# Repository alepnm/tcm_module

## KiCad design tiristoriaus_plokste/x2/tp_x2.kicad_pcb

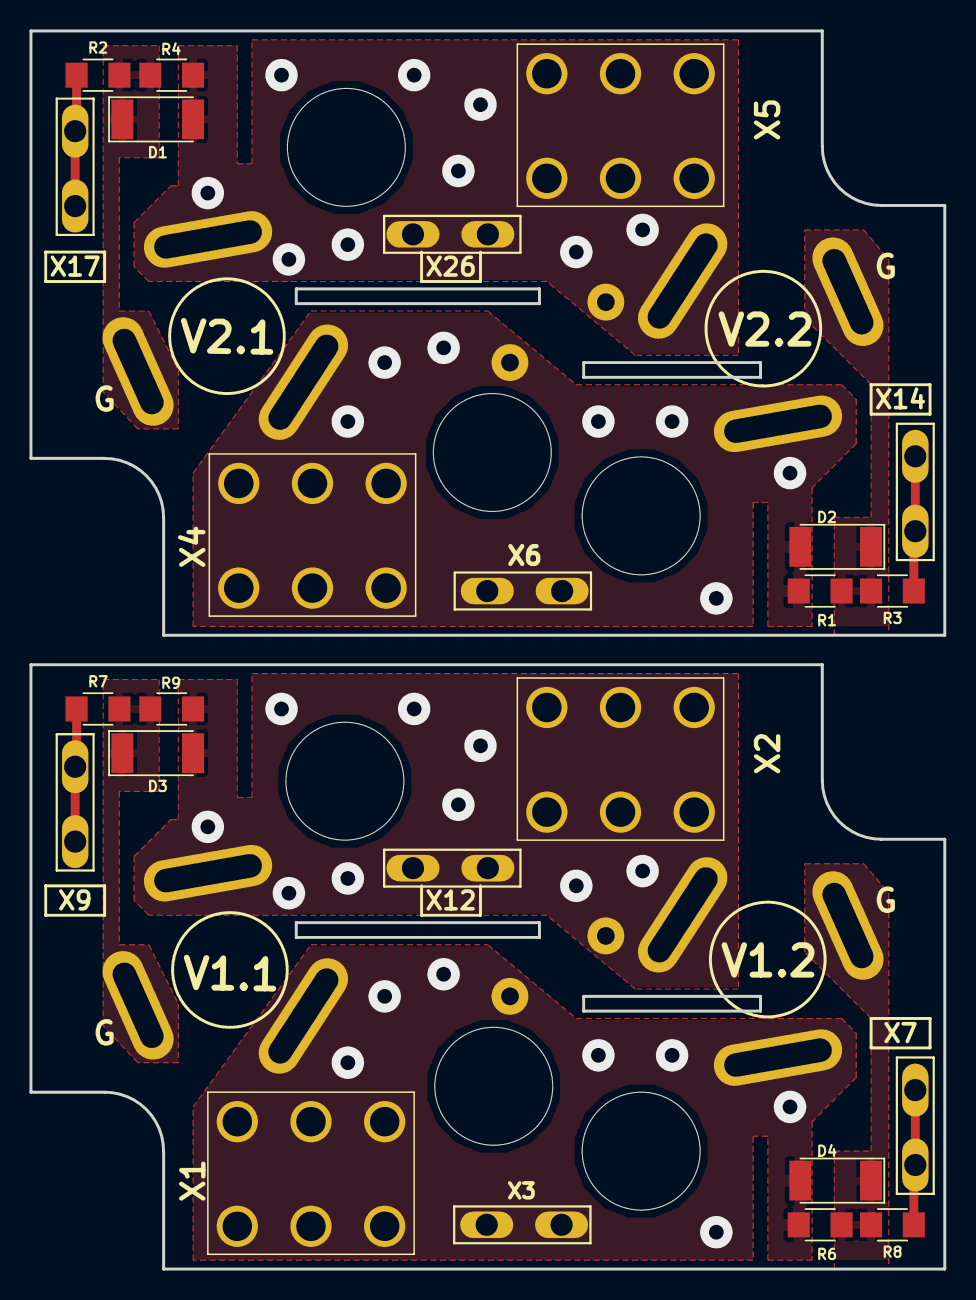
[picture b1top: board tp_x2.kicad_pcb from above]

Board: 2 copper layers, 62.0 x 84.0 mm, 32 parts (0 on the bottom side), 12 nets.

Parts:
D1, D2, D3, D4: LL4007; D_MELF
H1, H2, H3, H4: Conn_01x01; SolderWirePad_single_1mmDrill
R1, R4, R6, R9: 1k; R_1206
R2, R3, R7, R8: 470R; R_1206
V1.1, V1.2, V2.1, V2.2: BTW67; RD91
X1: LD1; Solder_Terminal_M3
X2: PH1; Solder_Terminal_M3
X3, X6, X7, X9, X12, X14, X17, X26: Faston_6.3x08x14; Faston_6.3x0.8x14
X4: LD3; Solder_Terminal_M3
X5: PH3; Solder_Terminal_M3

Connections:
/CTRL1A: R7.1, X9.1
/CTRL1B: R8.1, X7.1
/CTRL3A: R2.1, X17.1
/CTRL3B: R3.1, X14.1
/LD1: D4.2, H1.1, R6.1, V1.1.1, V1.2.3, X1.1, X3.1
/LD3: D2.2, H3.1, R1.1, V2.1.1, V2.2.3, X4.1, X6.1
/PH1: D3.2, H2.1, R9.1, V1.1.3, V1.2.1, X2.1, X12.1
/PH3: D1.2, H4.1, R4.1, V2.1.3, V2.2.1, X5.1, X26.1
unnamed: D1.1, R2.2, R4.2, V2.1.2
unnamed: D2.1, R1.2, R3.2, V2.2.2
unnamed: D3.1, R7.2, R9.2, V1.1.2
unnamed: D4.1, R6.2, R8.2, V1.2.2

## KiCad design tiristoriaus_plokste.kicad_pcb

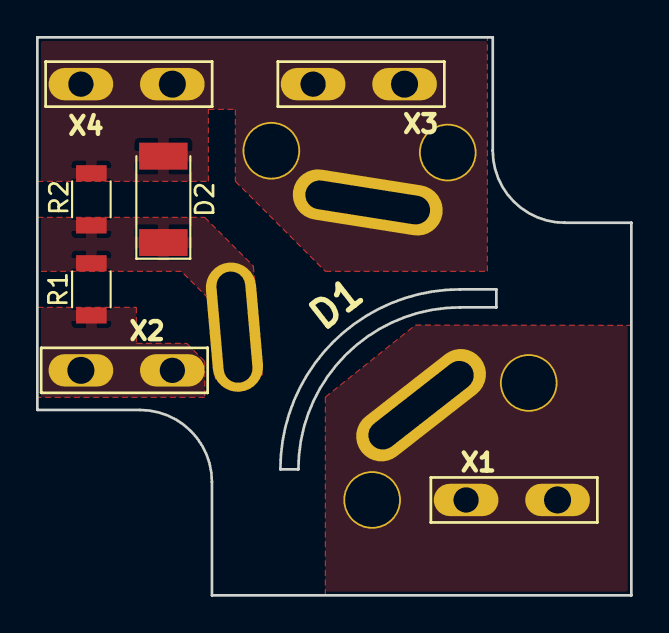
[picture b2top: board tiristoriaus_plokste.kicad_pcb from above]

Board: 2 copper layers, 33.0 x 31.0 mm, 8 parts (0 on the bottom side), 4 nets, no tracks yet.

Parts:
D1: BTW67; RD91
D2: LL4007; D_MELF
R1: 470R; R_1206
R2: 1k; R_1206
X1: A; Faston_6.3x0.8x14
X2, X4: Faston_6.3x08x14; Faston_6.3x0.8x14
X3: K; Faston_6.3x0.8x14

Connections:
/A: D1.1, X1.1
/C: D1.3, D2.2, R2.1, X3.1, X4.1
/CTRL: R1.1, X2.1
unnamed: D1.2, D2.1, R1.2, R2.2

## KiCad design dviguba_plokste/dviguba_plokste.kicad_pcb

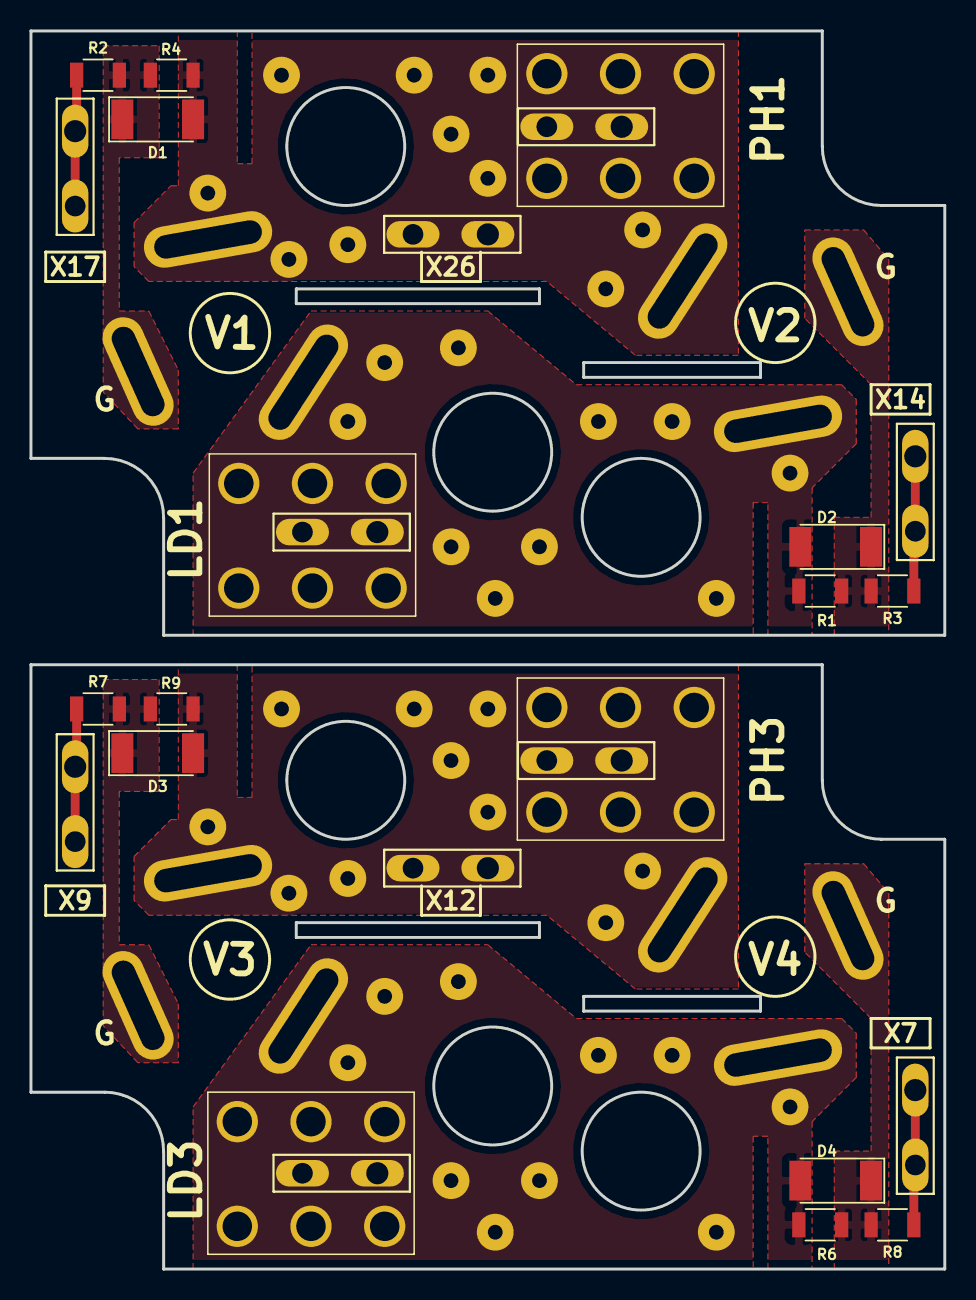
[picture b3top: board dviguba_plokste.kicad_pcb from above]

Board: 2 copper layers, 62.0 x 84.0 mm, 70 parts (0 on the bottom side), 12 nets.

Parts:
D1, D2, D3, D4: LL4007; D_MELF
H1, H2, H3, H4, H5, H6, H7, H8, H9, H10, H11, H12, H13, H14, H15, H16, H17, H18, H19, H20, H21, H22, H23, H24, H25, H26, H27, H28, H29, H30, H32, H33, H34, H35, H36, H37, H38, H39, H40: Conn_01x01; SolderWirePad_single_1mmDrill
H31: eConn_01x01; SolderWirePad_single_1mmDrill
R1, R4, R6, R9: 1k; R_1206
R2, R3, R7, R8: 470R; R_1206
V1, V2, V3, V4: BTW67; RD91
X1: LD3; Solder_Terminal_M6
X2: PH3; Solder_Terminal_M6
X3, X6, X7, X8, X9, X10, X12, X14, X17, X26: Faston_6.3x08x14; Faston_6.3x0.8x14
X4: LD1; Solder_Terminal_M6
X5: PH1; Solder_Terminal_M6

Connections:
/CTRL1A: R2.1, X17.1
/CTRL1B: R3.1, X14.1
/CTRL3A: R7.1, X9.1
/CTRL3B: R8.1, X7.1
/LD1: D2.2, H1.1, H2.1, H3.1, H4.1, H5.1, H6.1, H7.1, H8.1, H9.1, H10.1, R1.1, V1.1, V2.3, X3.1, X4.1
/LD3: D4.2, H21.1, H22.1, H23.1, H24.1, H25.1, H26.1, H27.1, H28.1, H29.1, H30.1, R6.1, V3.1, V4.3, X1.1, X8.1
/PH1: D1.2, H11.1, H12.1, H13.1, H14.1, H15.1, H16.1, H17.1, H18.1, H19.1, H20.1, R4.1, V1.3, V2.1, X5.1, X6.1, X26.1
/PH3: D3.2, H31.1, H32.1, H33.1, H34.1, H35.1, H36.1, H37.1, H38.1, H39.1, H40.1, R9.1, V3.3, V4.1, X2.1, X10.1, X12.1
unnamed: D1.1, R2.2, R4.2, V1.2
unnamed: D2.1, R1.2, R3.2, V2.2
unnamed: D3.1, R7.2, R9.2, V3.2
unnamed: D4.1, R6.2, R8.2, V4.2

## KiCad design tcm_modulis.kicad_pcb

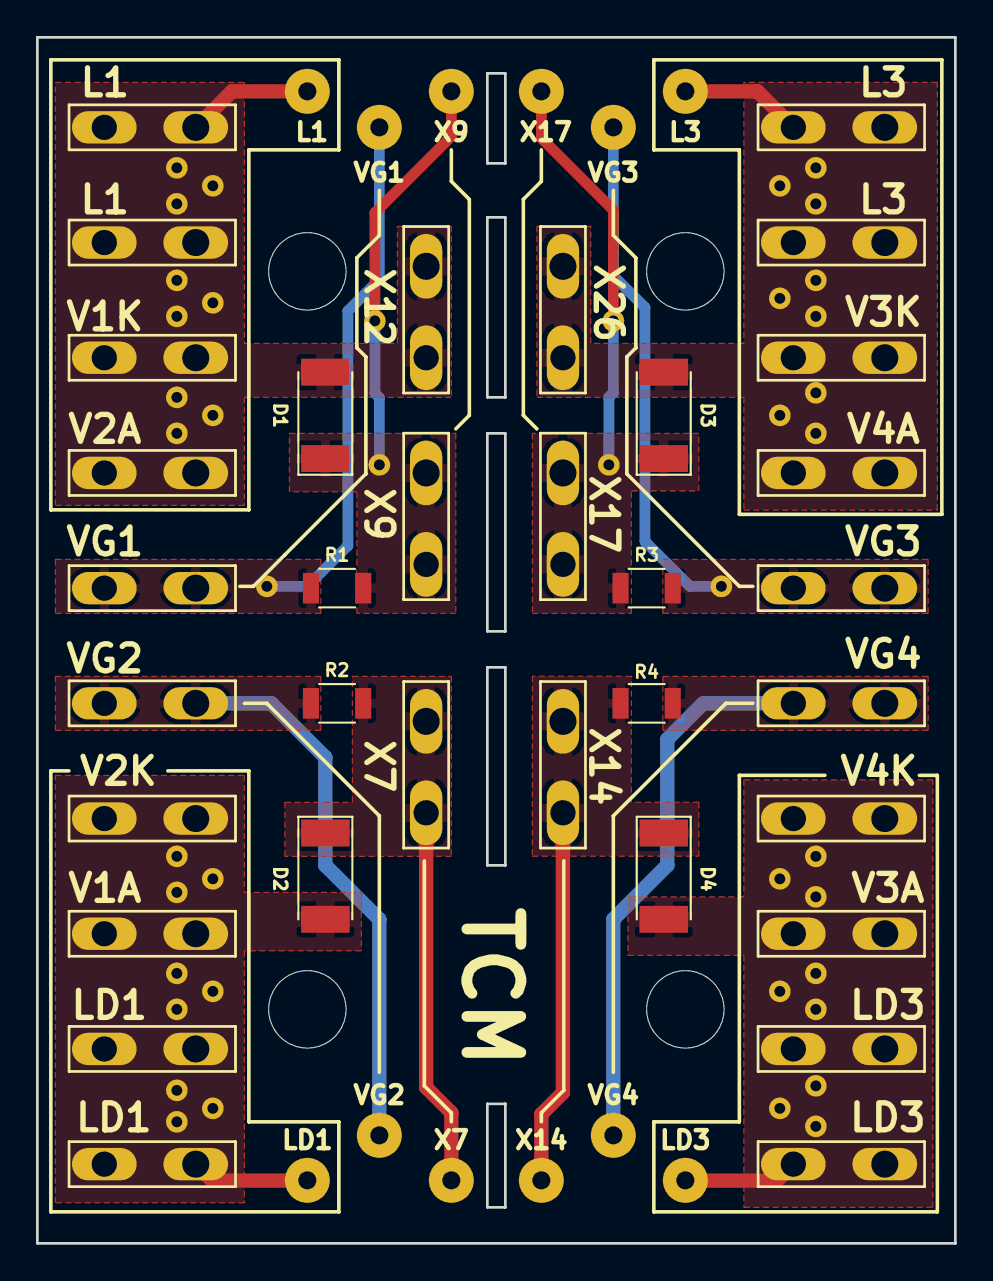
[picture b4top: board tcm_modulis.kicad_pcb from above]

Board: 2 copper layers, 51.0 x 67.0 mm, 34 parts (0 on the bottom side), 12 nets.

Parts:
D1, D2, D3, D4: LL4007; D_MELF
L11, L12, L31, L32: Faston_6.3x08x14; Faston_6.3x0.8x14
LD11, LD12, LD31, LD32: Faston_6.3x08x14; Faston_6.3x0.8x14
R1, R2, R3, R4: 330R; R_1206
V1A1, V1K1, V2A1, V2K1, V3A1, V3K1, V4A1, V4K1: Faston_6.3x08x14; Faston_6.3x0.8x14
VG1, VG2, VG3, VG4: Faston_6.3x08x14; Faston_6.3x0.8x14
X7, X9, X12, X14, X17, X26: Faston_6.3x08x14; Faston_6.3x0.8x14

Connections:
/IN1: D1.1, R1.2, X9.1
/IN2: D2.1, R2.2, X7.1
/IN3: D3.1, R3.2, X17.1
/IN4: D4.1, R4.2, X14.1
/L1: D1.2, L11.1, L12.1, V1K1.1, V2A1.1, X12.1
/L3: D3.2, L31.1, L32.1, V3K1.1, V4A1.1, X26.1
/LD1: D2.2, LD11.1, LD12.1, V1A1.1, V2K1.1
/LD3: D4.2, LD31.1, LD32.1, V3A1.1, V4K1.1
/VG1: R1.1, VG1.1
/VG2: R2.1, VG2.1
/VG3: R3.1, VG3.1
/VG4: R4.1, VG4.1

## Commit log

2018-07-04 pradine inicializacija
2018-07-04 sugeneruoti gerberiai
2018-07-04 paruosta surinkimo schema
2018-09-27 nauja tiristoriu plokste. 3d step failas tcm modulio
2018-10-05 pataisyti RD91 futprinto kontaktai, schemoje papiestos lygiagretaus simistoriu pajungimo schemos, ir komutavimas jais trifaziu apkrovu
2018-10-11 plokstes dviem tiristoriams projektavimas. gerber failu ruosimas gamybai
2018-10-18 paruosti failai gamybai
2018-11-05 sugeneruoti nauji gerberiai, paruostos principine ir surinkimo schemos.
2018-11-05 sugeneruoti nauji gerberiai, paruostos principine, komponentu isdestymo ir surinkimo schemos.
2018-11-05 gamybos failu paruosimas
2018-11-19 paskutinis variantas. sugeneruoti nauji gerberiai
2018-12-19 tiristoriu plokste EKA'ms
2019-02-07 failai gamybai: peek&place, nauji gerberiai - panelei, breziniai
2019-02-08 paruosta gamybai - plokstes sugrupuoti panelemis, paruosti peek-and-place failai
2019-02-20 pasalinti nereikalingi failai
2019-04-29 2019-04-28
